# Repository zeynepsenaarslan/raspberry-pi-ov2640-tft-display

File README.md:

# raspberry-pi-ov2640-tft-display
Real-time camera streaming system on Raspberry Pi using OV2640 camera and ST7735 TFT display.

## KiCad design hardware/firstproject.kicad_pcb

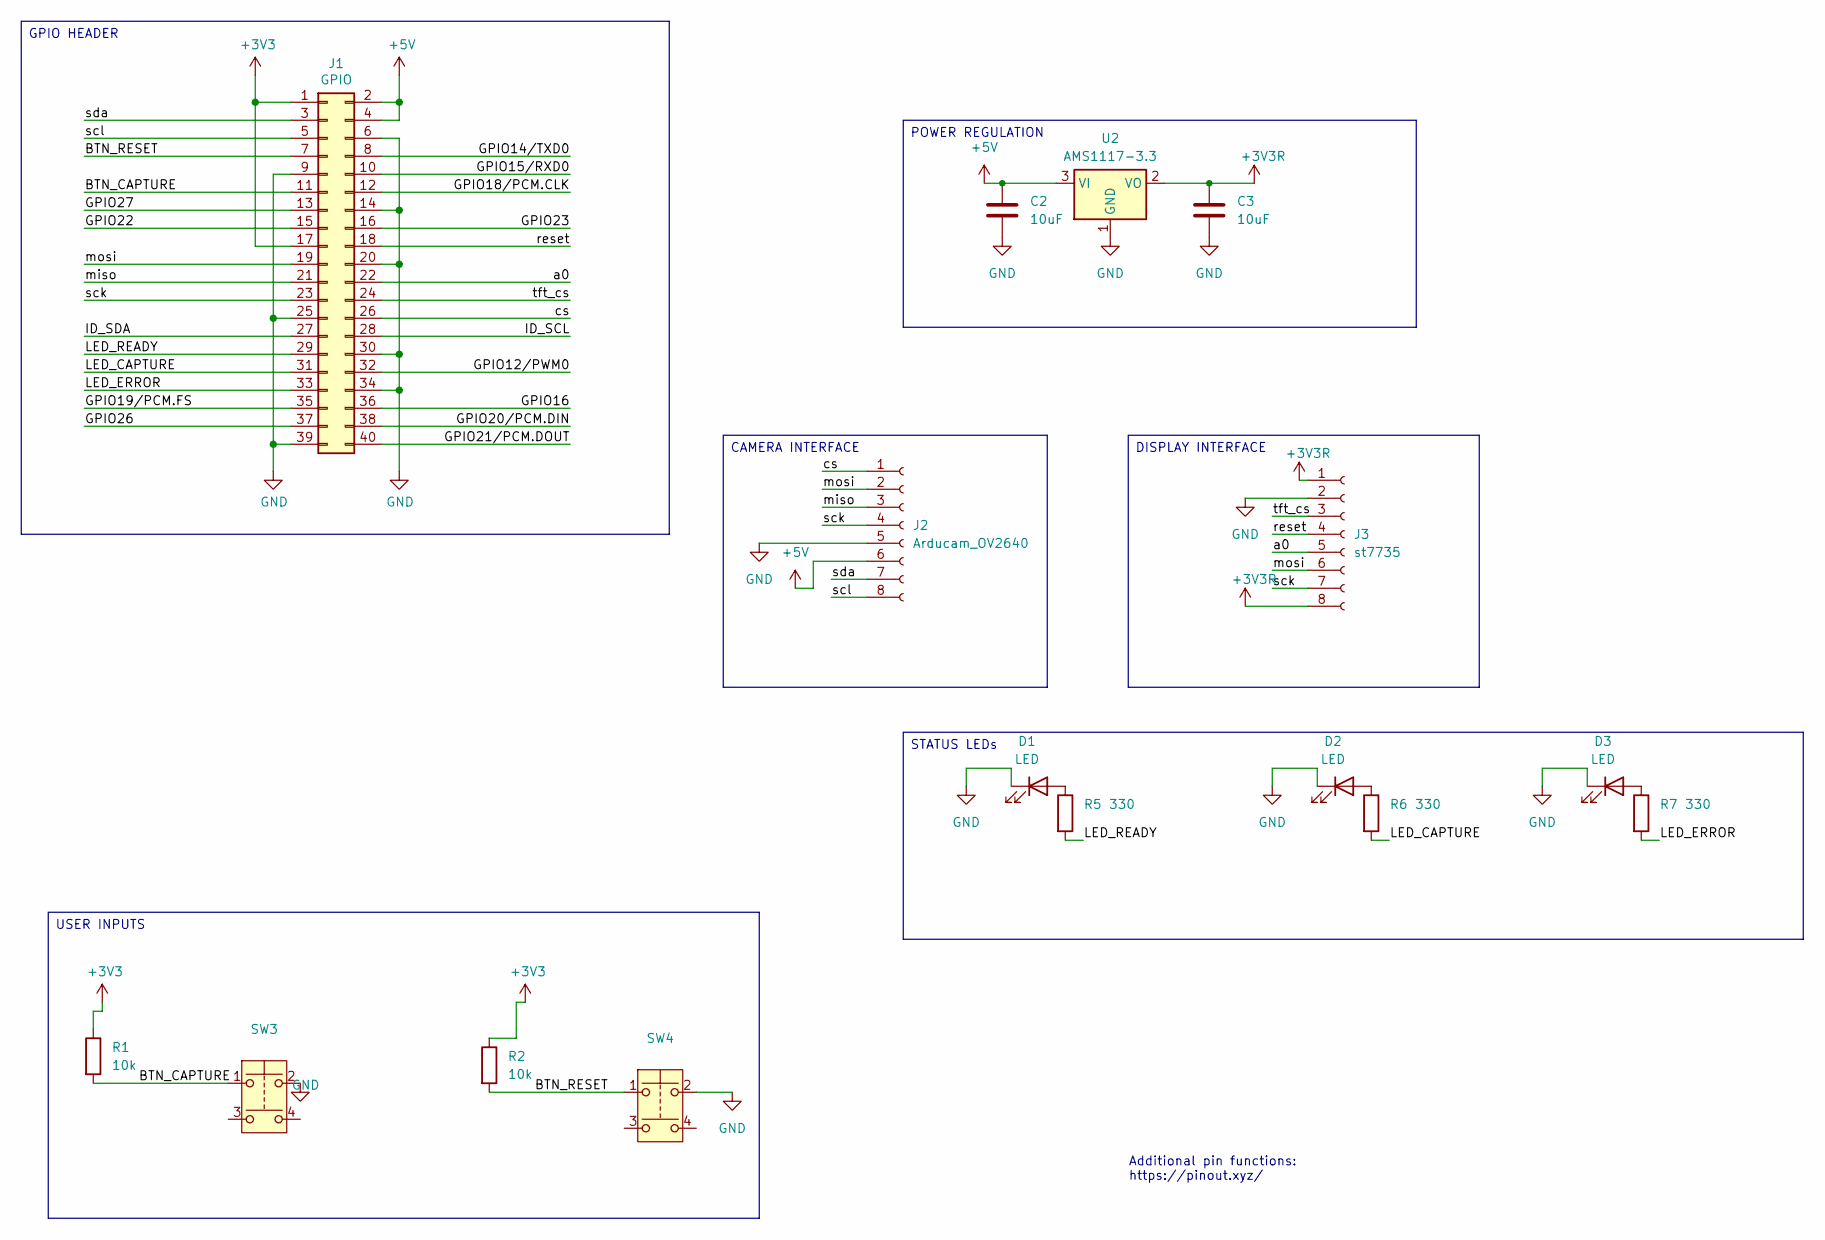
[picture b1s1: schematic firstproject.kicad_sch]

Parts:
C2, C3: 10uF; C_0805_2012Metric
D1, D2, D3: LED; LED_0805_2012Metric
J1: GPIO; PinSocket_2x20_P2.54mm_Vertical
J2: Arducam_OV2640; Molex_KK-254_AE-6410-08A_1x08_P2.54mm_Vertical
J3: st7735; Molex_KK-254_AE-6410-08A_1x08_P2.54mm_Vertical
R1, R2: 10k; R_0805_2012Metric_Pad1.20x1.40mm_HandSolder
R5, R6, R7: 330; R_0805_2012Metric
SW3, SW4: SW_Push_Dual; SW_Push_1P1T_NO_CK_KSC7xxJ
U2: AMS1117-3.3; SOT-223-3_TabPin2

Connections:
+3V3: J1.1, J1.17, R1.1, R2.1
+3V3R: C3.1, J3.1, J3.8, U2.2 (VO)
+5V: C2.1, J1.2, J1.4, J2.6, U2.3 (VI)
/BTN_CAPTURE: J1.11, R1.2, SW3.1
/BTN_RESET: J1.7, R2.2, SW4.1
/GPIO12/PWM0: J1.32
/GPIO14/TXD0: J1.8
/GPIO15/RXD0: J1.10
/GPIO16: J1.36
/GPIO18/PCM.CLK: J1.12
/GPIO19/PCM.FS: J1.35
/GPIO20/PCM.DIN: J1.38
/GPIO21/PCM.DOUT: J1.40
/GPIO22: J1.15
/GPIO23: J1.16
/GPIO26: J1.37
/GPIO27: J1.13
/ID_SCL: J1.28
/ID_SDA: J1.27
/LED_CAPTURE: J1.31, R6.2
/LED_ERROR: J1.33, R7.2
/LED_READY: J1.29, R5.2
/a0: J1.22, J3.5
/cs: J1.26, J2.1
/miso: J1.21, J2.3
/mosi: J1.19, J2.2, J3.6
/reset: J1.18, J3.4
/sck: J1.23, J2.4, J3.7
/scl: J1.5, J2.8
/sda: J1.3, J2.7
/tft_cs: J1.24, J3.3
GND: C2.2, C3.2, D1.1 (K), D2.1 (K), D3.1 (K), J1.6, J1.9, J1.14, J1.20, J1.25, J1.30, J1.34, J1.39, J2.5, J3.2, SW3.2, SW4.2, U2.1 (GND)
unnamed: D1.2 (A), R5.1
unnamed: D2.2 (A), R6.1
unnamed: D3.2 (A), R7.1

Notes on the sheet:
Additional pin functions: https://pinout.xyz/
CAMERA INTERFACE
STATUS LEDs
DISPLAY INTERFACE
GPIO HEADER
POWER REGULATION
USER INPUTS

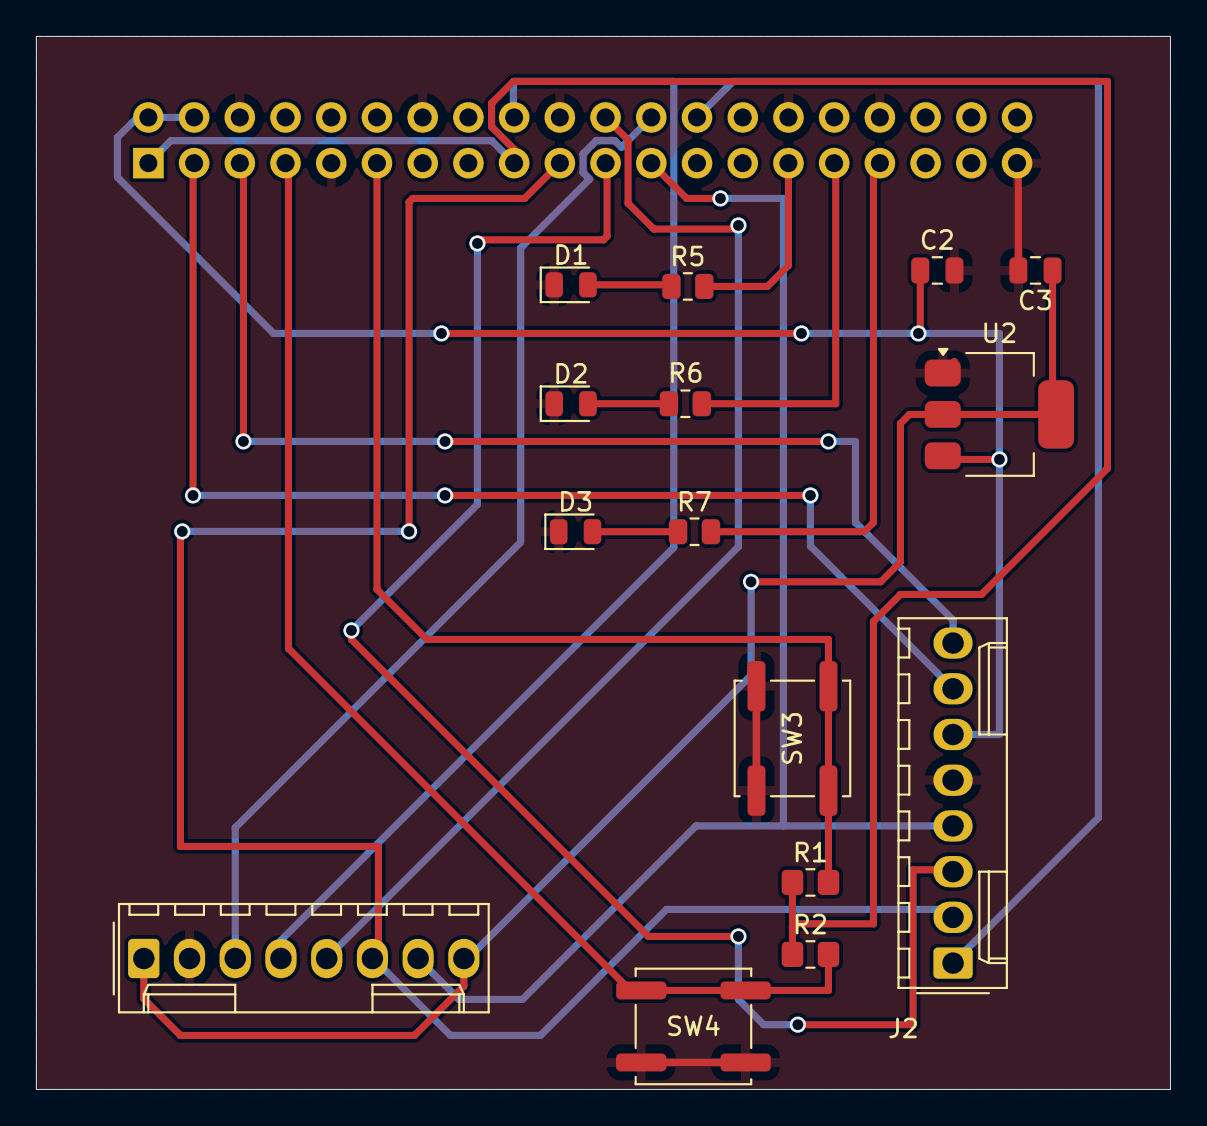
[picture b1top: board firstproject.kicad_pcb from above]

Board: 2 copper layers, 63.0 x 58.5 mm, 16 parts (1 on the bottom side), 21 nets.

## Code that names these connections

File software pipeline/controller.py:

#!/usr/bin/env python3
# controller.py — Buton + LED + TFT warm-up + cam2tft real-time kontrol

import RPi.GPIO as GPIO
import subprocess
import time
import os
def wait_dev(path, tries=200, delay=0.1):
    for _ in range(tries):
        if os.path.exists(path):
            return True
        time.sleep(delay)
    return False

# Pinler (BCM numaraları)
BTN_CAPTURE = 17   # pin 11
BTN_RESET   = 4    # pin 7

LED_READY   = 5    # pin 29
LED_CAPTURE = 6    # pin 31
LED_ERROR   = 13   # pin 33

# Bu yolları kendi sistemine göre ayarla:
CAM2TFT_PATH   = "/home/admin/cam2tft"
TFT_TEST_PATH  = "/home/admin/tft_ok.py"   # daha önce kullandığın "TFT OK" python dosyası
TFT_PYTHON     = "/home/admin/tftenv/bin/python"

# Arka planda çalışan cam2tft süreci
cam_proc = None


def init_gpio():
    GPIO.setmode(GPIO.BCM)

    # Butonlar: pull-up (boşta iken 1, bastığında 0)
    GPIO.setup(BTN_CAPTURE, GPIO.IN, pull_up_down=GPIO.PUD_UP)
    GPIO.setup(BTN_RESET,   GPIO.IN, pull_up_down=GPIO.PUD_UP)

    # LED'ler: çıkış
    GPIO.setup(LED_READY,   GPIO.OUT)
    GPIO.setup(LED_CAPTURE, GPIO.OUT)
    GPIO.setup(LED_ERROR,   GPIO.OUT)

    # Başlangıçta her şeyi kapat
    GPIO.output(LED_READY,   0)
    GPIO.output(LED_CAPTURE, 0)
    GPIO.output(LED_ERROR,   0)


def tft_warmup():
    """Ekranı ayağa kaldırmak için TFT test scriptini bir kez çalıştır."""
    if not os.path.exists(TFT_TEST_PATH):
        print(f"UYARI: {TFT_TEST_PATH} bulunamadı, TFT warm-up atlanıyor.")
        return

    print("TFT warm-up: tft_ok.py çalıştırılıyor...")
    try:
        subprocess.run([TFT_PYTHON, TFT_TEST_PATH], check=True)
        print("TFT warm-up tamam.")
    except subprocess.CalledProcessError as e:
        print("UYARI: tft_ok.py hata ile bitti, return code:", e.returncode)


def start_preview():
    global cam_proc

    if cam_proc is not None and cam_proc.poll() is None:
        return

    if not wait_dev("/dev/spidev0.0") or not wait_dev("/dev/spidev0.1") or not wait_dev("/dev/i2c-1"):
        print("SPI/I2C cihazları gelmedi (PCB takılı değil olabilir).")
        GPIO.output(LED_ERROR, 1)
        return

    print("cam2tft (preview) baslatiliyor...")
    try:
        cam_proc = subprocess.Popen(["sudo", CAM2TFT_PATH])
        GPIO.output(LED_READY, 1)
        GPIO.output(LED_CAPTURE, 0)
        GPIO.output(LED_ERROR, 0)
    except Exception as e:
        print("cam2tft baslatma hatasi:", e)
        GPIO.output(LED_ERROR, 1)
        cam_proc = None



def stop_preview():
    """cam2tft sürecini durdur (son kare ekranda kalır)."""
    global cam_proc

    if cam_proc is None:
        return

    if cam_proc.poll() is None:
        print("cam2tft durduruluyor (freeze)...")
        try:
            cam_proc.terminate()
            try:
                cam_proc.wait(timeout=1.0)
            except subprocess.TimeoutExpired:
                print("cam2tft takıldı, kill gönderiliyor...")
                cam_proc.kill()
        except Exception as e:
            print("cam2tft durdurma hatası:", e)

    cam_proc = None


def main():
    init_gpio()

    # Başlangıçta TFT warm-up yap
    tft_warmup()

    # Başta canlı preview başlat
    start_preview()

    print("Sistem hazır.")
    print("Canlı önizleme açık.")
    print("Fotoğrafı 10 sn dondurmak için BTN_CAPTURE (GPIO17)'ye bas.")
    print("TFT+kamera warm-up için BTN_RESET (GPIO4)'e bas.")

    try:
        while True:
            # RESET butonu (aktif low)
            if GPIO.input(BTN_RESET) == GPIO.LOW:
                print("Reset butonuna basıldı, preview durdur + TFT warm-up...")
                GPIO.output(LED_READY,   0)
                GPIO.output(LED_CAPTURE, 0)
                GPIO.output(LED_ERROR,   0)

                # Önce cam2tft'yi durdur
                stop_preview()

                # TFT warm-up tekrar
                tft_warmup()

                # Tekrar preview başlat
                start_preview()

                # butonu bırakmasını bekle (debounce)
                while GPIO.input(BTN_RESET) == GPIO.LOW:
                    time.sleep(0.05)

            # CAPTURE butonu (aktif low)
            if GPIO.input(BTN_CAPTURE) == GPIO.LOW:
                print("Capture butonuna basıldı -> 5 sn freeze mod")

                # LED durumları
                GPIO.output(LED_READY,   0)
                GPIO.output(LED_CAPTURE, 1)
                GPIO.output(LED_ERROR,   0)

                # 1) canlı preview'i durdur -> son kare ekranda donmuş kalır
                stop_preview()

                # 2) 10 saniye boyunca görüntü aynı kalsın
                time.sleep(5)

                # 3) tekrar canlı preview'e geç
                GPIO.output(LED_CAPTURE, 0)
                start_preview()

                # Butonu bırakmasını bekle (debounce)
                while GPIO.input(BTN_CAPTURE) == GPIO.LOW:
                    time.sleep(0.05)

            time.sleep(0.02)

    finally:
        print("Çıkılıyor, cam2tft durduruluyor ve GPIO temizleniyor...")
        stop_preview()
        GPIO.cleanup()


if __name__ == "__main__":
    main()

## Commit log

2026-03-11 Create hardware
2026-03-11 Create software pipeline
2026-03-11 Create cam2tft
2026-03-11 Rename cam2tft to cam2tft.c
